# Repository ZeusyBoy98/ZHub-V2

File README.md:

# ZHub-V2
A complex USB 3.2 Hub to suite my needs.
Made for Hack Club Fallout

## Zine

## What?
A basic USB hub with:
<ul>
<li> 1 Upstream USB-C
<li> 1 Downstream USB-C 3.2
<li> 2 Downstream USB-A 3.2
<li> 2 Downstream USB-C 2.0
<li> 2 Downstream USB-A 2.0
<li> USB 2.0 because I used a very basic chip
</ul>

## Why?
Because I don't have any USB-C USB hubs and A to C adapters are annoying. If I can just have one good USB hub on me at all times, that can allow me to plug all the stuff I could possibly need in, then that achieves my goal.

## How?
In order to make this project for yourself, you'll need to purchase the board and get it assembled through PCBA with all the components below (PCB manufacturer-acceptable BOM at PCB/Gerbers/bom.csv). You'll also have to 3D print the case.
| Quantity | Item                    | URL                                               | Unit Price ($USD) | Total Price ($USD) |
| -------- | ----------------------- | ------------------------------------------------- | ----------------- | ------------------ |
| 5        | CoreChips SL2.1A        | https://www.lcsc.com/product-detail/C192893.html  | 0.2522            | 1.26               |
| 10       | USB A 2.0 Receptacle    | https://www.lcsc.com/product-detail/C668591.html  | 0.0667            | 0.67               |
| 20       | USB C 2.0 Receptacle    | https://www.lcsc.com/product-detail/C2765186.html | 0.0666            | 1.33               |
| 100      | 1uf Capacitor           | https://www.lcsc.com/product-detail/C107372.html  | 0.0019            | 0.19               |
| 100      | 100nf Capacitor         | https://www.lcsc.com/product-detail/C309458.html  | 0.0012            | 0.12               |
| 100      | 5.1k Resistor           | https://www.lcsc.com/product-detail/C2906874.html | 0.0006            | 0.06               |
| 5        | TUSB8042A               | https://www.lcsc.com/product-detail/C2860610.html | 8.1684            | 40.84              |
| 10       | USB A 3.1 Receptacle    | https://www.lcsc.com/product-detail/C309458.html  | 0.23              | 2.3                |
| 5        | USB C 3.2 Receptacle    | https://www.lcsc.com/product-detail/C134092.html  | 1.0565            | 5.28               |
| 20       | ESD Diode               | https://www.lcsc.com/product-detail/C82044.html   | 0.0359            | 0.72               |
| 10       | 24Mhz Crystal           | https://www.lcsc.com/product-detail/C5444545.html | 0.0615            | 0.62               |
| 10       | Polyfuse                | https://www.lcsc.com/product-detail/C883135.html  | 0.0616            | 0.62               |
| 10       | 22uf Capacitor          | https://www.lcsc.com/product-detail/C105226.html  | 0.0455            | 0.46               |
| 100      | 18pf Capacitor          | https://www.lcsc.com/product-detail/C106202.html  | 0.0012            | 0.12               |
| 100      | 10uf Capacitor          | https://www.lcsc.com/product-detail/C315248.html  | 0.0092            | 0.92               |
| 10       | 9.53k Resistor          | https://www.lcsc.com/product-detail/C6127312.html | 0.0682            | 0.68               |
| 100      | 4.7k Resistor           | https://www.lcsc.com/product-detail/C105871.html  | 0.0008            | 0.08               |
| 100      | 43k Resistor            | https://www.lcsc.com/product-detail/C185415.html  | 0.001             | 0.10               |
| 100      | 1M Resistor             | https://www.lcsc.com/product-detail/C138033.html  | 0.0009            | 0.09               |
| 5        | 220@100MHz Ferrite Bead | https://www.lcsc.com/product-detail/C454099.html  | 0.151             | 0.76               |
| 5        | 3.3V Buck Converter     | https://www.lcsc.com/product-detail/C780769.html  | 0.4705            | 2.35               |
| PCB      |                         |                                                   | 5.2               | 5.2                |
| PCBA     |                         |                                                   | 145.82            | 145.82             |
| Shipping |                         |                                                   |                   | 10.51              |
| Total    |                         |                                                   |                   | 161.53             |

### Build Guide:

#### 1. Preparation<br>
Before starting, make sure you have:
<ul>
<li>The gerbers, pick and place file, and BOM, all available in this repository at (PCB/production)
<li>A 3D printer (or get the printed parts from someone else)
</ul>

#### 2. Ordering
Go to your PCB manufacturer of choice (Make sure they have PCBA) and follow their instructions on how to order.

#### 3. Case
3D print the print file, CAD/ZHub-V2-Print.3mf <br>
This has all the case parts you need (top and bottom)

#### 4. Assembly
Once the case has finished printing, place the assembled PCB into said case, then get the lid and slide it into the grooves of the bottom half of the case to close it.

#### 5. Profit
Plug a USB-C to C cable into the upstream port of the hub (the one not next to any other ports), and plug the other end of that cable into your computer. Then plug whatever USB devices into the downstream ports and...

This project does not need firmware, so you're good to go!

Enjoy your ZHub!!!

## Renders

## Designing

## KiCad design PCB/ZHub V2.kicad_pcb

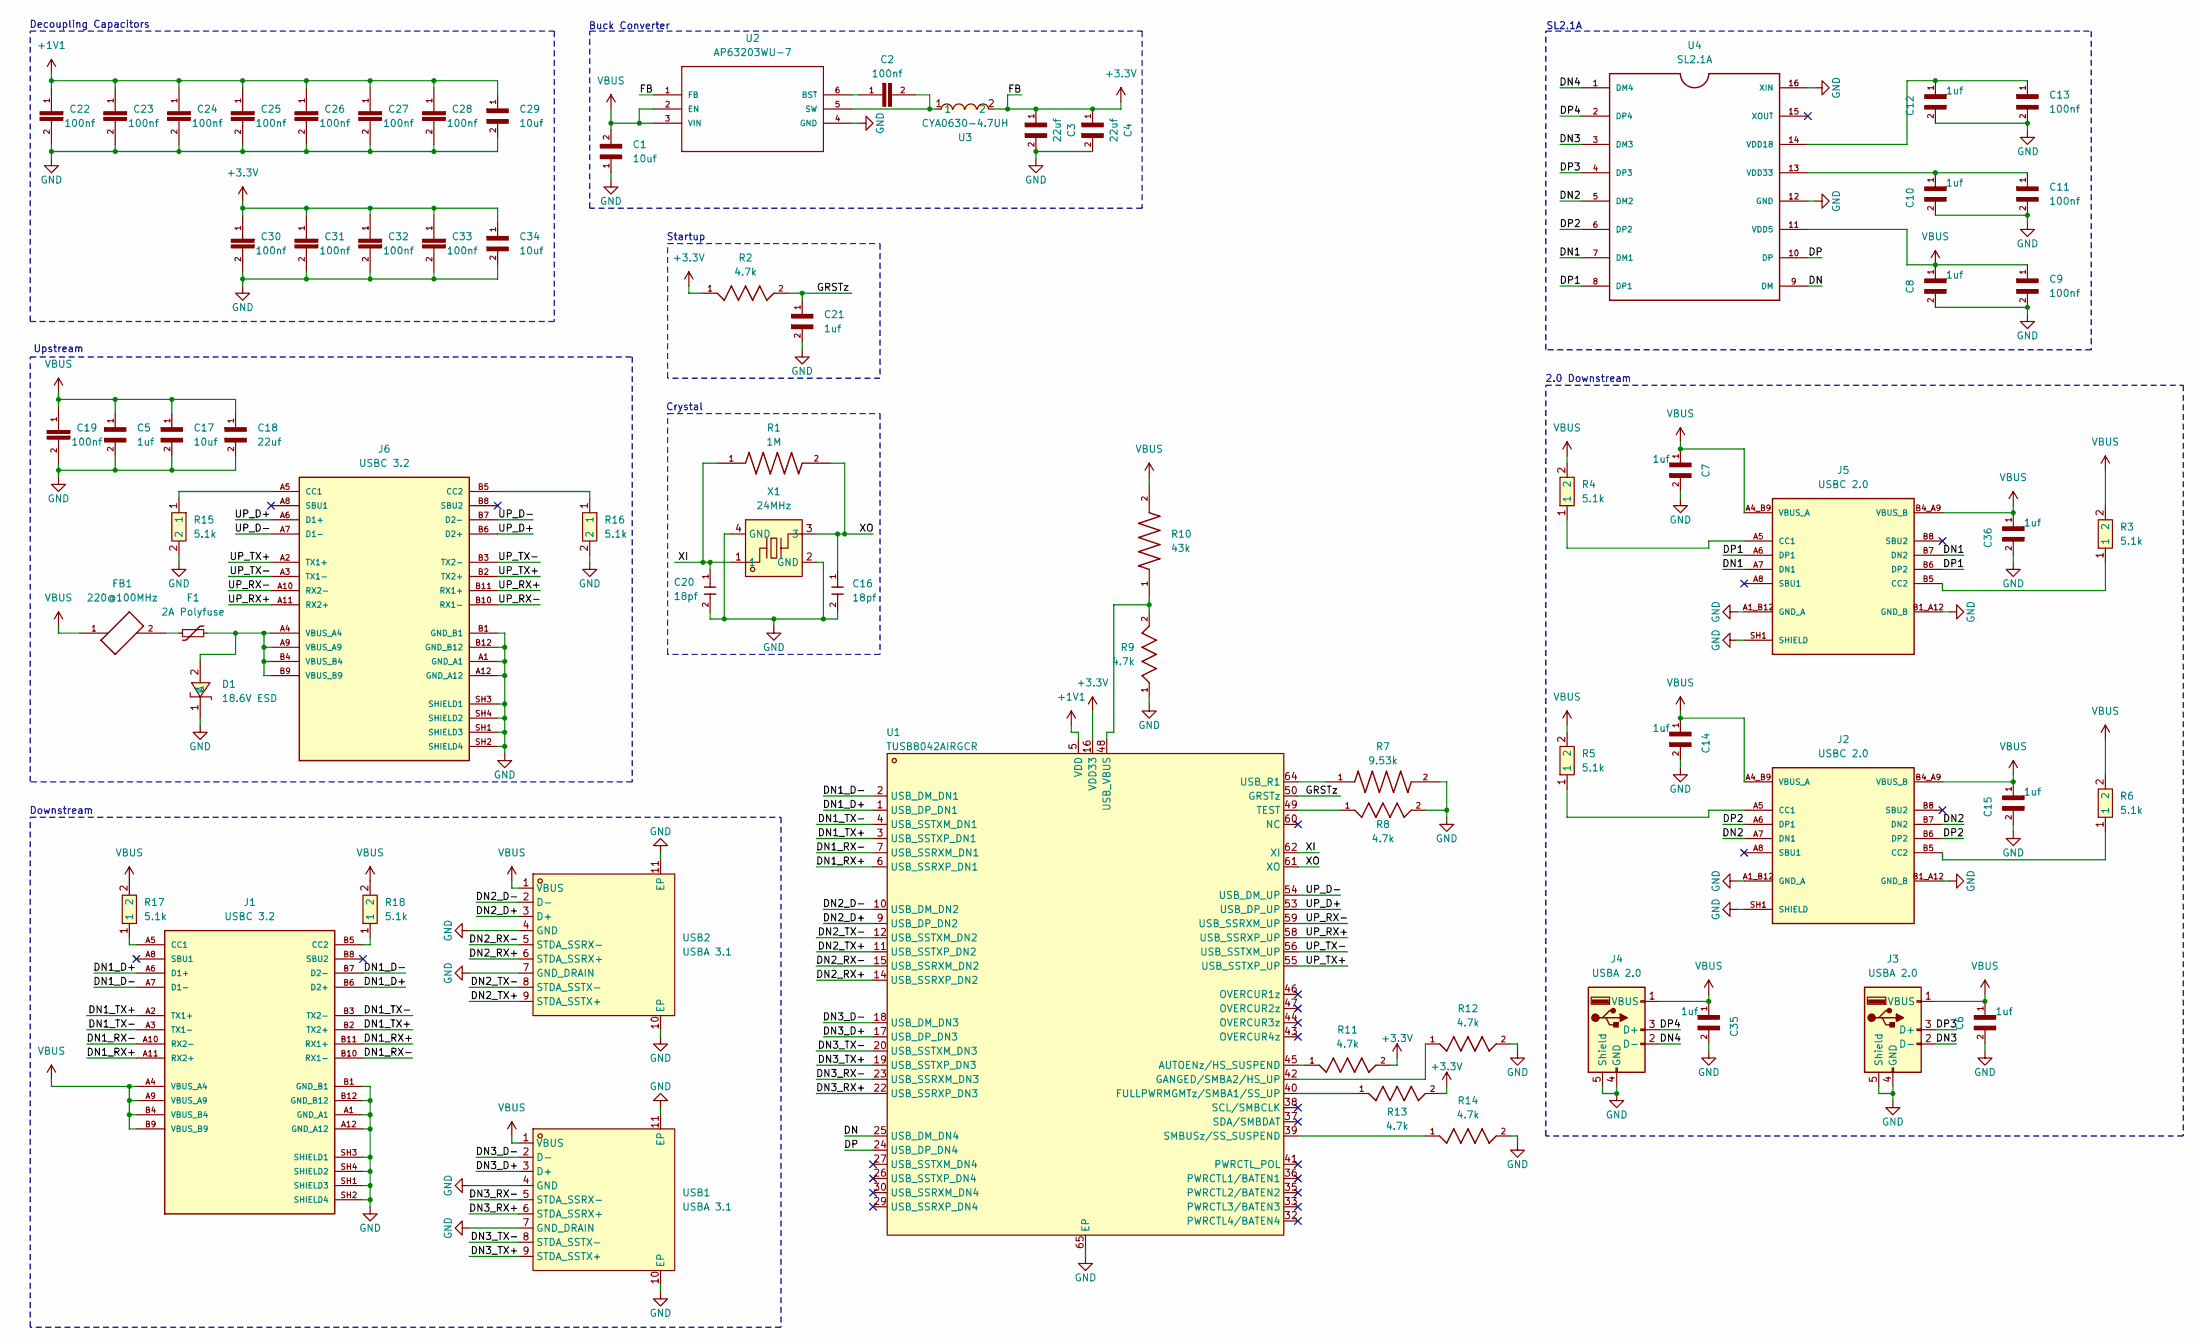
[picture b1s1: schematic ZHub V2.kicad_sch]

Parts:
C1, C17, C29, C34: 10uf; 10uf_10V_0402
C2, C19, C22, C23, C24, C25, C26, C27, C28, C30, C31, C32, C33: 100nf; 100nf_10V_0402
C3, C4, C18: 22uf; 22uf_6.3V_0402
C5, C21: 1uf; 1uf_6.3V_0402
C6, C7, C8, C10, C12, C14, C15, C35, C36: 1uf; 1uf_0402
C9, C11, C13: 100nf; 100nf_0402; DigiKey_Part_Number 399-C1210V104KCRACTUCT-ND
C16, C20: 18pf; 18pf_15V_0402; MPN CC0402JRNPO9BN180
D1: 18.6V ESD; SOD-523F_L1.2-W0.8-LS1.7-RD; LCSC Part C82044
F1: 2A Polyfuse; 1210
FB1: 220@100MHz; 220_100MHz_bead
J1, J6: USBC 3.2; MOLEX_3.2_TYPEC; PARTREV A7
J2, J5: USBC 2.0; SHOUHAN_TYPE-C_16PIN_2MD__073_; PARTREV A
J3, J4: USBA 2.0; USB-A-TH_10.0QHHTZB6.3
R1: 1M; 1M_50V_0402; PARTREV Nov-2024
R2, R8, R9, R11, R12, R13, R14: 4.7k; 4.7k_50V_0402
R3, R4, R5, R6: 5.1k; R0402; PARTREV 3/1/2020; LCSC Part C2906874
R7: 9.53k; 9.53k_0402; PARTREV V6
R10: 43k; 43k_50V_0402; DigiKey_Part_Number 311-43.0KLRCT-ND
R15, R16, R17, R18: 5.1k; R0402; LCSC Part C2906874
U1: TUSB8042AIRGCR; VQFN-64_L9.0-W9.0-P0.50-TL-EP6.0; LCSC Part C2860610
U2: AP63203WU-7; 3.3V_buck; MPN AP63203WU-7
U3: CYA0630-4.7UH; 5A_4.7uH_Inductor; LCSC Part C5189748
U4: SL2.1A; SLA2.1s
USB1, USB2: USBA 3.1; USB-A-SMD_U-A-39WD-W-1; LCSC Part C3020886
X1: 24MHz; CRYSTAL-SMD_4P-L3.2-W2.5-BL; LCSC Part C5444545

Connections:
+1V1: C22.1, C23.1, C24.1, C25.1, C26.1, C27.1, C28.1, C29.1, U1.5 (VDD), U1.8 (VDD), U1.13 (VDD), U1.21 (VDD), U1.28 (VDD), U1.31 (VDD), U1.51 (VDD), U1.57 (VDD)
+3.3V: C3.1, C4.1, C30.1, C31.1, C32.1, C33.1, C34.1, R2.1, R11.2, R13.2, U1.16 (VDD33), U1.34 (VDD33), U1.52 (VDD33), U1.63 (VDD33), U2.1 (FB), U3.2
/DN: U1.25 (USB_DM_DN4), U4.9 (DM)
/DN1: J5.A7 (DN1), J5.B7 (DN2), U4.7 (DM1)
/DN1_D+: J1.A6 (D1+), J1.B6 (D2+), U1.1 (USB_DP_DN1)
/DN1_D-: J1.A7 (D1-), J1.B7 (D2-), U1.2 (USB_DM_DN1)
/DN1_RX+: J1.A11 (RX2+), J1.B11 (RX1+), U1.6 (USB_SSRXP_DN1)
/DN1_RX-: J1.A10 (RX2-), J1.B10 (RX1-), U1.7 (USB_SSRXM_DN1)
/DN1_TX+: J1.A2 (TX1+), J1.B2 (TX2+), U1.3 (USB_SSTXP_DN1)
/DN1_TX-: J1.A3 (TX1-), J1.B3 (TX2-), U1.4 (USB_SSTXM_DN1)
/DN2: J2.A7 (DN1), J2.B7 (DN2), U4.5 (DM2)
/DN2_D+: U1.9 (USB_DP_DN2), USB2.3 (D+)
/DN2_D-: U1.10 (USB_DM_DN2), USB2.2 (D-)
/DN2_RX+: U1.14 (USB_SSRXP_DN2), USB2.6 (STDA_SSRX+)
/DN2_RX-: U1.15 (USB_SSRXM_DN2), USB2.5 (STDA_SSRX-)
/DN2_TX+: U1.11 (USB_SSTXP_DN2), USB2.9 (STDA_SSTX+)
/DN2_TX-: U1.12 (USB_SSTXM_DN2), USB2.8 (STDA_SSTX-)
/DN3: J3.2 (D-), U4.3 (DM3)
/DN3_D+: U1.17 (USB_DP_DN3), USB1.3 (D+)
/DN3_D-: U1.18 (USB_DM_DN3), USB1.2 (D-)
/DN3_RX+: U1.22 (USB_SSRXP_DN3), USB1.6 (STDA_SSRX+)
/DN3_RX-: U1.23 (USB_SSRXM_DN3), USB1.5 (STDA_SSRX-)
/DN3_TX+: U1.19 (USB_SSTXP_DN3), USB1.9 (STDA_SSTX+)
/DN3_TX-: U1.20 (USB_SSTXM_DN3), USB1.8 (STDA_SSTX-)
/DN4: J4.2 (D-), U4.1 (DM4)
/DP: U1.24 (USB_DP_DN4), U4.10 (DP)
/DP1: J5.A6 (DP1), J5.B6 (DP2), U4.8 (DP1)
/DP2: J2.A6 (DP1), J2.B6 (DP2), U4.6 (DP2)
/DP3: J3.3 (D+), U4.4 (DP3)
/DP4: J4.3 (D+), U4.2 (DP4)
/GRSTz: C21.1, R2.2, U1.50 (GRSTz)
/UP_D+: J6.A6 (D1+), J6.B6 (D2+), U1.53 (USB_DP_UP)
/UP_D-: J6.A7 (D1-), J6.B7 (D2-), U1.54 (USB_DM_UP)
/UP_RX+: J6.A11 (RX2+), J6.B11 (RX1+), U1.58 (USB_SSRXP_UP)
/UP_RX-: J6.A10 (RX2-), J6.B10 (RX1-), U1.59 (USB_SSRXM_UP)
/UP_TX+: J6.A2 (TX1+), J6.B2 (TX2+), U1.55 (USB_SSTXP_UP)
/UP_TX-: J6.A3 (TX1-), J6.B3 (TX2-), U1.56 (USB_SSTXM_UP)
/XI: C20.1, R1.1, U1.62 (XI), X1.1
/XO: C16.1, R1.2, U1.61 (XO), X1.3
GND: C1.1, C3.2, C4.2, C5.2, C6.2, C7.2, C8.2, C9.2, C10.2, C11.2, C12.2, C13.2, C14.2, C15.2, C16.2, C17.2, C18.2, C19.2, C20.2, C21.2, C22.2, C23.2, C24.2, C25.2, C26.2, C27.2, C28.2, C29.2, C30.2, C31.2, C32.2, C33.2, C34.2, C35.2, C36.2, D1.1 (C), J1.A1 (GND_A1), J1.A12 (GND_A12), J1.B1 (GND_B1), J1.B12 (GND_B12), J1.SH1 (SHIELD3), J1.SH2 (SHIELD4), J1.SH3 (SHIELD1), J1.SH4 (SHIELD2), J2.A1_B12 (GND_A), J2.B1_A12 (GND_B), J2.SH1 (SHIELD), J2.SH2 (SHIELD), J2.SH3 (SHIELD), J2.SH4 (SHIELD), J3.4 (GND), J3.5 (Shield), J3.6, J4.4 (GND), J4.5 (Shield), J4.6, J5.A1_B12 (GND_A), J5.B1_A12 (GND_B), J5.SH1 (SHIELD), J5.SH2 (SHIELD), J5.SH3 (SHIELD), J5.SH4 (SHIELD), J6.A1 (GND_A1), J6.A12 (GND_A12), J6.B1 (GND_B1), J6.B12 (GND_B12), J6.SH1 (SHIELD3), J6.SH2 (SHIELD4), J6.SH3 (SHIELD1), J6.SH4 (SHIELD2), R7.2, R8.2, R9.1, R12.2, R14.2, R15.2, R16.2, U1.65 (EP), U2.4 (GND), U4.12 (GND), U4.16 (XIN), USB1.4 (GND), USB1.7 (GND_DRAIN), USB1.10 (EP), USB1.11 (EP), USB2.4 (GND), USB2.7 (GND_DRAIN), USB2.10 (EP), USB2.11 (EP), X1.2 (GND), X1.4 (GND)
unnamed: D1.2 (A), F1.2, J6.A4 (VBUS_A4), J6.A9 (VBUS_A9), J6.B4 (VBUS_B4), J6.B9 (VBUS_B9)
unnamed: F1.1, FB1.2
unnamed: J1.A5 (CC1), R17.1
unnamed: J1.B5 (CC2), R18.1
unnamed: J2.A5 (CC1), R5.1
unnamed: J2.B5 (CC2), R6.1
unnamed: J5.A5 (CC1), R4.1
unnamed: J5.B5 (CC2), R3.1
unnamed: J6.A5 (CC1), R15.1
unnamed: J6.B5 (CC2), R16.1
unnamed: R11.1, U1.45 (AUTOENz/HS_SUSPEND)
unnamed: R13.1, U1.40 (FULLPWRMGMTz/SMBA1/SS_UP)
unnamed: R12.1, U1.42 (GANGED/SMBA2/HS_UP)
unnamed: R14.1, U1.39 (SMBUSz/SS_SUSPEND)
unnamed: R8.1, U1.49 (TEST)
unnamed: R7.1, U1.64 (USB_R1)
unnamed: R9.2, R10.1, U1.48 (USB_VBUS)
unnamed: C2.1, U2.6 (BST)
unnamed: C2.2, U2.5 (SW), U3.1
unnamed: C12.1, C13.1, U4.14 (VDD18)
unnamed: C10.1, C11.1, U4.13 (VDD33)
VBUS: C1.2, C5.1, C6.1, C7.1, C8.1, C9.1, C14.1, C15.1, C17.1, C18.1, C19.1, C35.1, C36.1, FB1.1, J1.A4 (VBUS_A4), J1.A9 (VBUS_A9), J1.B4 (VBUS_B4), J1.B9 (VBUS_B9), J2.A4_B9 (VBUS_A), J2.B4_A9 (VBUS_B), J3.1 (VBUS), J4.1 (VBUS), J5.A4_B9 (VBUS_A), J5.B4_A9 (VBUS_B), R3.2, R4.2, R5.2, R6.2, R10.2, R17.2, R18.2, U2.2 (EN), U2.3 (VIN), U4.11 (VDD5), USB1.1 (VBUS), USB2.1 (VBUS)

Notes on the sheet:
2.0 Downstream
Startup
Buck Converter
Downstream
Upstream
SL2.1A
Crystal
Decoupling Capacitors

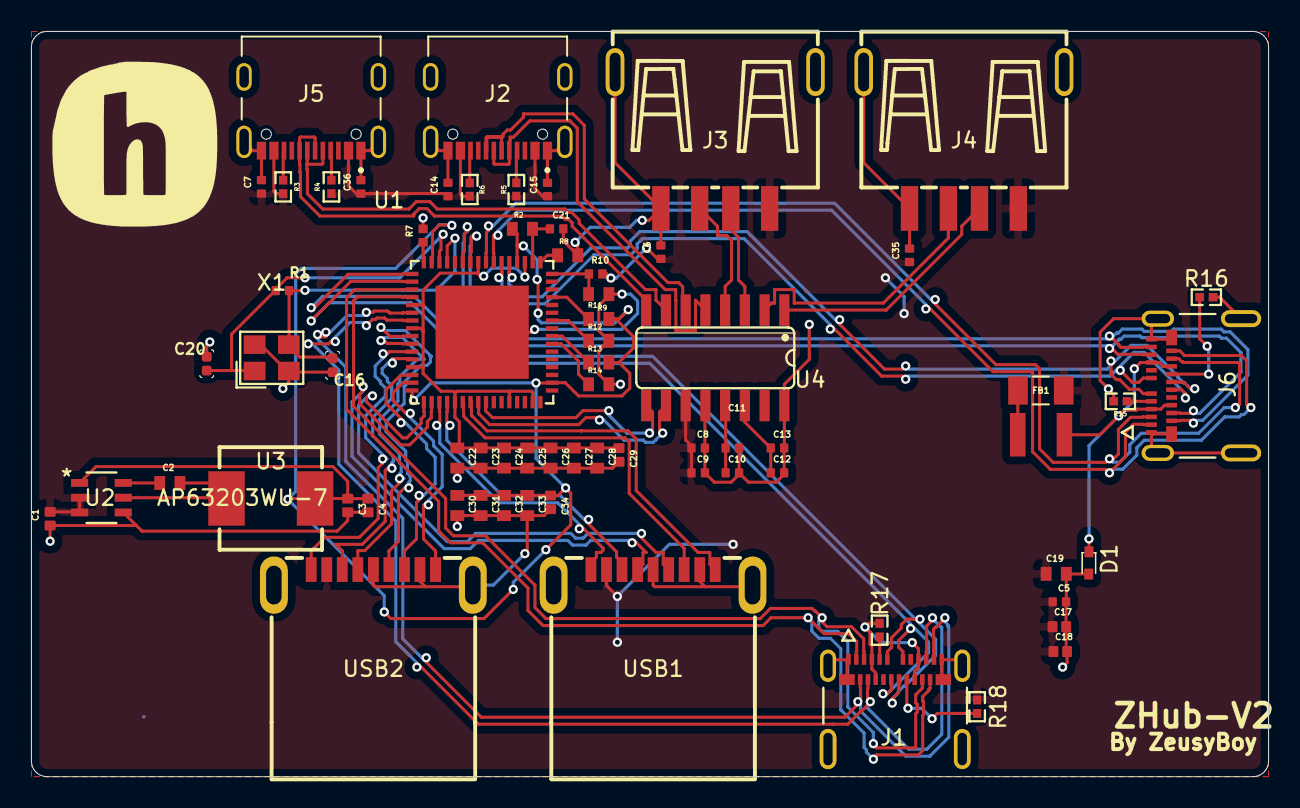
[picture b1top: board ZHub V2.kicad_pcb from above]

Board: 2 copper layers, 79.6 x 48.0 mm, 70 parts (0 on the bottom side), 62 nets.

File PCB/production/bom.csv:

Comment,Designator,Footprint,LCSC Part Number
USBC 3.2,"J1,J6",USB C SMD,C134092
USBC 2.0,"J2,J5",USB C SMD,C2765186
USBA 3.1,"USB1, USB2",USB A SMD,C3020886
USBA 2.0,"J3,J4",USB A TH,C668591
TUSB8042AIRGCR,U1,VQFN-64,C2860610
SL2.1A,U4,SL2.1A,C192893
CYA0630-4.7UH,U3,7.2x6.6 SMD,C5189748
AP63203WU-7,U2,TSOT-23-6,C780769
9.53k,R7,0402,C6127312
5.1k,"R3,R4,R5,R6,R15,R16,R17,R18",0402,C2906874
43k,R10,0402,C185415
4.7k,"R11,R12,R13,R14,R2,R8,R9",0402,C105871
2A Polyfuse,F1,1206,C883135
24MHz,X1,SMD3225-4P,C5444545
22uf,"C18,C3,C4",0402,C105226
220@100MHz,FB1,1206,C454099
1uf,"C10,C12,C14,C15,C35,C36,C6,C7,C8,C21,C5",0402,C107372
1M,R1,0402,C138033
18pf,"C16,C20",0402,C106202
18.6V ESD,D1,SOD-523,C82044
10uf,"C1,C17,C29,C34",0402,C315248
100nf,"C19,C2,C22,C23,C24,C25,C26,C27,C28,C30,C31,C32,C33,C11,C13,C9",0402,C309458

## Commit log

2026-05-10 Finish schematic, PCB, and BOM
2026-05-16 Finish case
2026-05-18 Add actually good README
2026-05-18 Finished and added Zine
2026-05-18 Add path to production files
